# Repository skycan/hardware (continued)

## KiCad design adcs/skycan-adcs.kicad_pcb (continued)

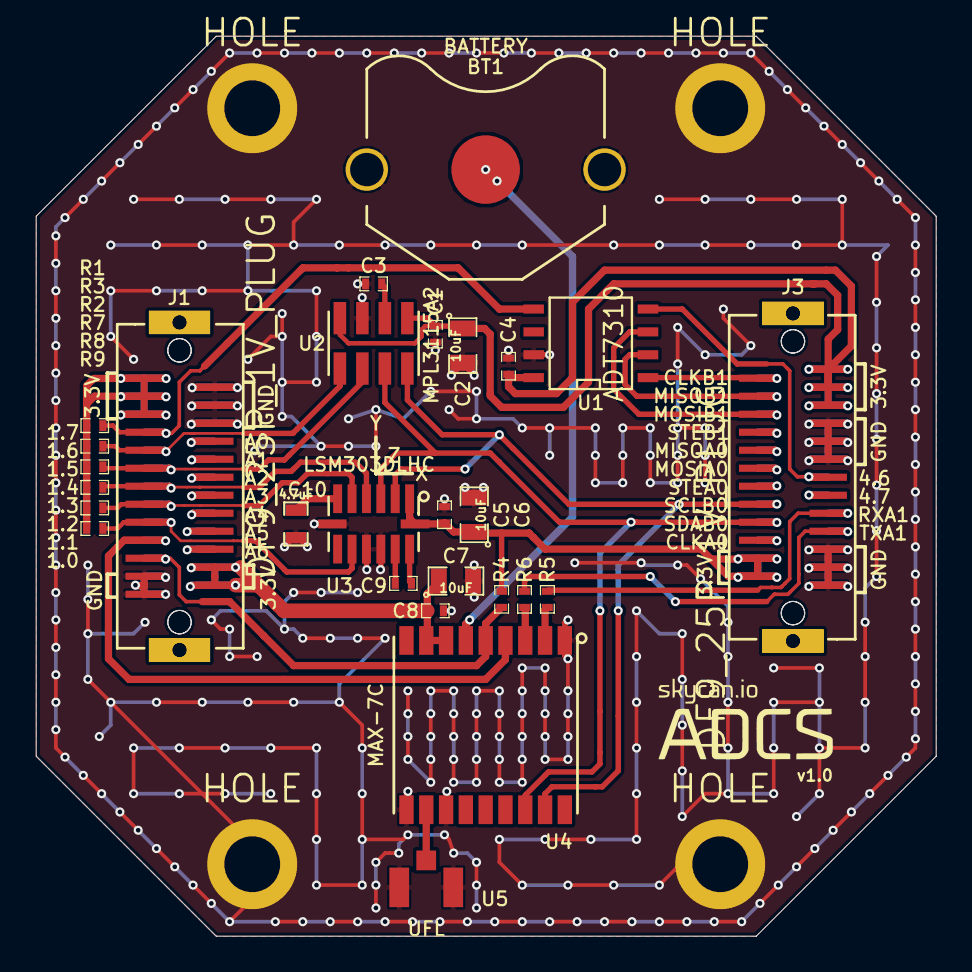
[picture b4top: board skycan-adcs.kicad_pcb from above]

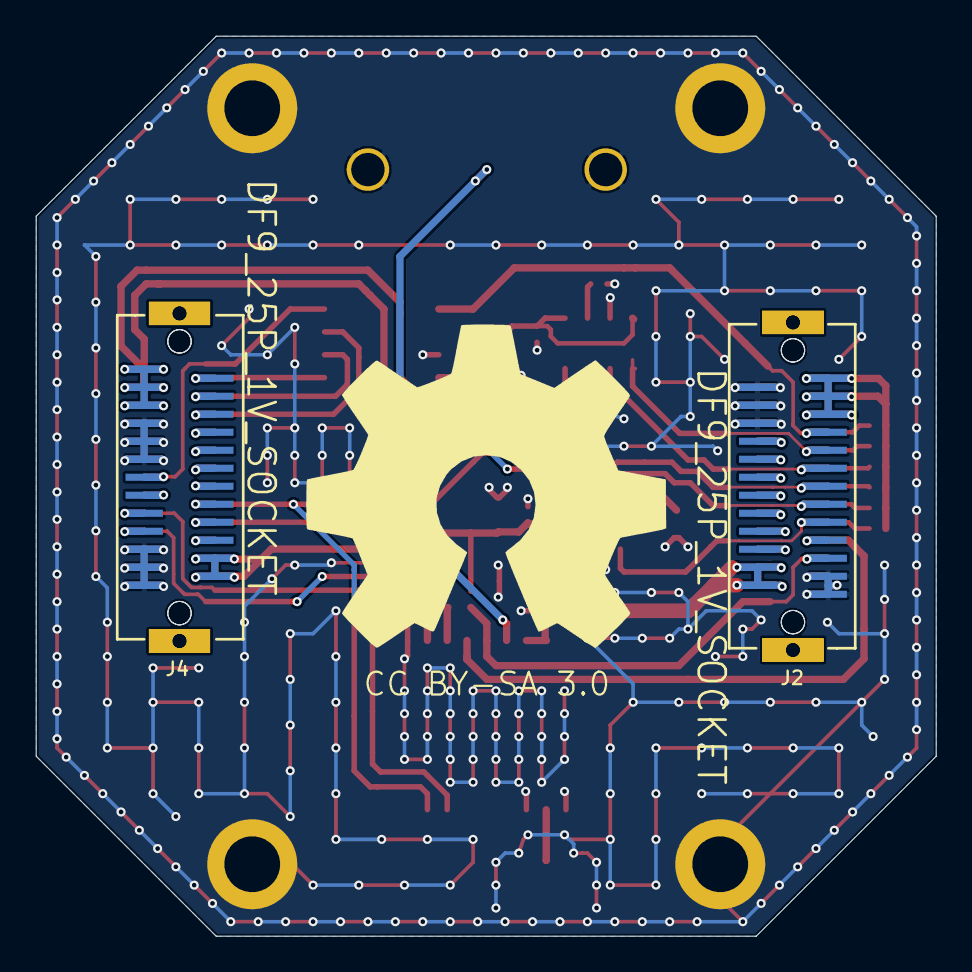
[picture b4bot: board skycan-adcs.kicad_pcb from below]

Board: 2 copper layers, 50.0 x 50.0 mm, 34 parts (2 on the bottom side), 39 nets.

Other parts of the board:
VAL: skycan-adcs-logo

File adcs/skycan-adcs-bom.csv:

Reference,Value,LibPart,Footprint,Qty,Farnell
BT1,BATTERY,device:BATTERY,,1,908642
"C1, C3, C4, C5, C8",100nF,device:C,0402,5,
C10,4.7uF,device:C,0603,1,
"C2, C6, C7",10uF,device:C,0603,3,
C9,220nF,device:C,0402,1,
"J1, J3",DF9_25P_1V_PLUG,skycan:DF9_25P_1V_PLUG,,2,1798379
"J2, J4",DF9_25P_1V_SOCKET,skycan:DF9_25P_1V_SOCKET,,2,1798380
"R1, R2, R3, R4, R7, R8, R9",4.7k,device:R,,7,
"R5, R6",330R,device:R,,2,
U1,ADT7310,skycan:ADT7310,SOIC8,1,2067805
U2,MPL3115A2,skycan:MPL3115A2,LGA8,1,2009084
U3,LSM303DLHC,skycan:LSM303DLHC,LGA-14,1,2068595
U4,MAX-7C,skycan:MAX-7C,,1,
U5,UFL,skycan:UFL,,1,1688077

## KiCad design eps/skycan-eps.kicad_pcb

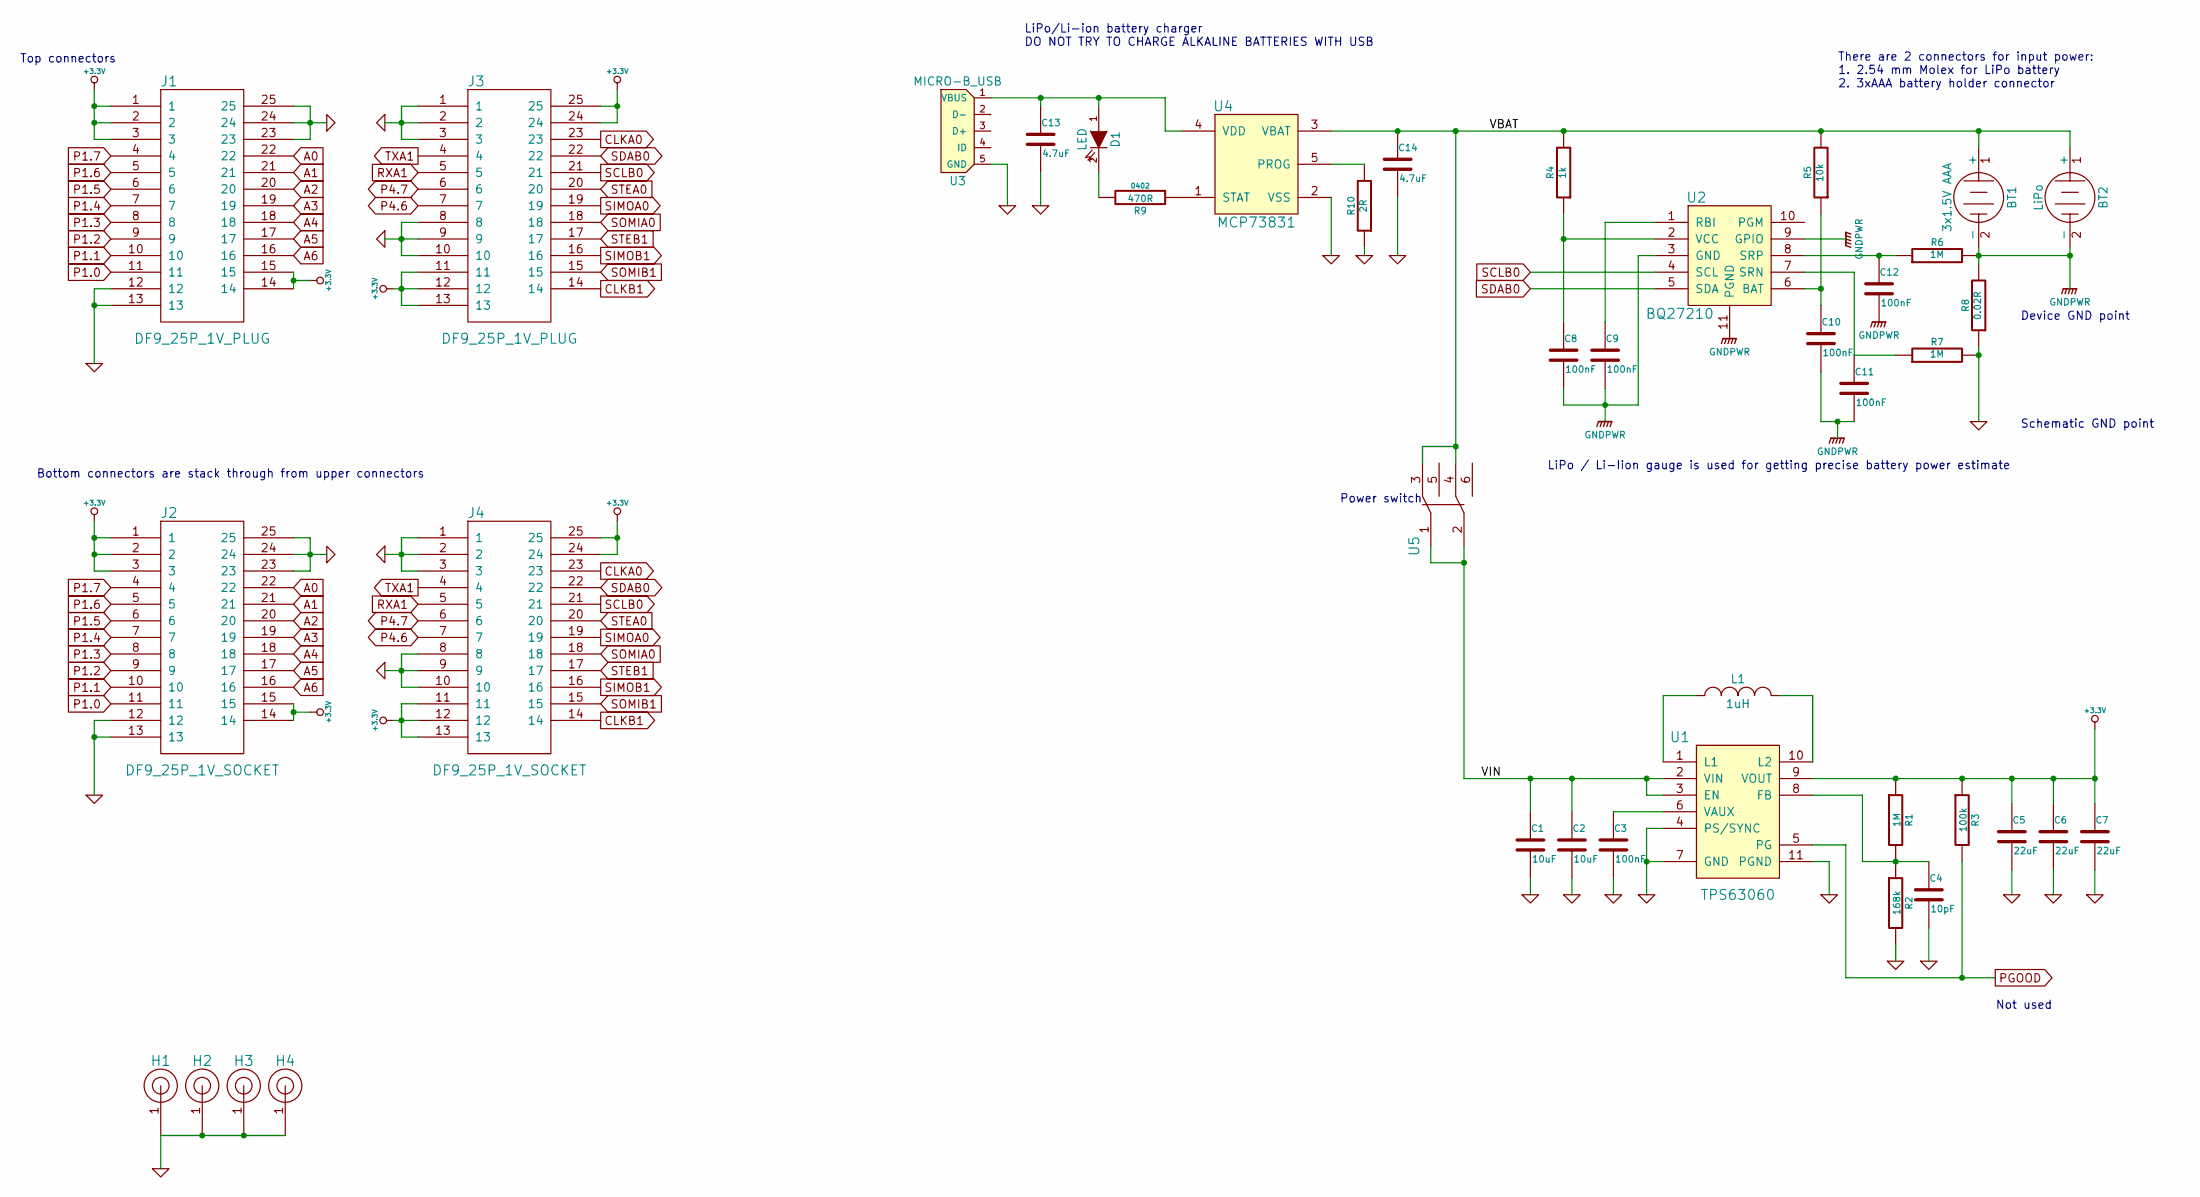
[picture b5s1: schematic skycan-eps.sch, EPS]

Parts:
BT1: 3x1.5V AAA; AA holder; Farnell 1339843
BT2: LiPo
C1, C2: 10uF; 0805
C3, C8, C9, C10, C11, C12: 100nF; 0402
C4: 10pF; 0402
C5, C6, C7: 22uF; 0805
C13, C14: 4.7uF; 0805
D1: LED; 0603
H1, H2, H3, H4: HOLE
J1, J3: DF9_25P_1V_PLUG; Farnell 1798379
J2, J4: DF9_25P_1V_SOCKET; Farnell 1798380
L1: 1uH; 4x4 mm; Farnell 2289214
R1, R6, R7: 1M; 0402
R2: 168k; 0402
R3: 100k; 0402
R4: 1k; 0402
R5: 10k; 0402
R8: 0.02R; 0603
R9: 470R; 0402
R10: 2R; 0402
U1: TPS63060; PWSON-N10; Farnell 2082430
U2: BQ27210; PVSON-N10; Farnell 1754768
U3: MICRO-B_USB; Farnell 2293753
U4: MCP73831; SOT-23-5; Farnell 1332158
U5: SWITCH-DPDT; Farnell 1522047

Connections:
+3.3V: C5.1, C6.1, C7.1, J1.1, J1.2, J1.3, J1.14, J1.15, J2.1, J2.2, J2.3, J2.14, J2.15, J3.11, J3.12, J3.13, J3.24, J3.25, J4.11, J4.12, J4.13, J4.24, J4.25, R1.1, R3.1, U1.9 (VOUT)
/VBAT: BT1.1 (+), BT2.1 (+), C14.1, R4.2, R5.2, U4.3 (VBAT), U5.3, U5.4
/VIN: C1.1, C2.1, U1.2 (VIN), U1.3 (EN), U5.1, U5.2
A0: J1.22, J2.22
A1: J1.21, J2.21
A2: J1.20, J2.20
A3: J1.19, J2.19
A4: J1.18, J2.18
A5: J1.17, J2.17
A6: J1.16, J2.16
CLKA0: J3.23, J4.23
CLKB1: J3.14, J4.14
GND: C1.2, C2.2, C3.2, C4.2, C5.2, C6.2, C7.2, C13.2, C14.2, H1.1, H2.1, H3.1, H4.1, J1.12, J1.13, J1.23, J1.24, J1.25, J2.12, J2.13, J2.23, J2.24, J2.25, J3.1, J3.2, J3.3, J3.8, J3.9, J3.10, J4.1, J4.2, J4.3, J4.8, J4.9, J4.10, R2.2, R7.2, R8.1, R10.1, U1.4 (PS/SYNC), U1.7 (GND), U1.11 (PGND), U3.5 (GND), U4.2 (VSS)
GNDPWR: BT1.2 (-), BT2.2 (-), C8.2, C9.2, C10.2, C11.2, C12.2, R6.2, R8.2, U2.3 (GND), U2.9 (GPIO), U2.11 (PGND)
unnamed: R9.1, U4.1 (STAT)
unnamed: D1.2 (K), R9.2
unnamed: C13.1, D1.1 (A), U3.1 (VBUS), U4.4 (VDD)
unnamed: C3.1, U1.6 (VAUX)
unnamed: C8.1, R4.1, U2.2 (VCC)
unnamed: C10.1, R5.1, U2.6 (BAT)
unnamed: C9.1, U2.1 (RBI)
unnamed: C11.1, R7.1, U2.7 (SRN)
unnamed: R10.2, U4.5 (PROG)
unnamed: L1.1, U1.1 (L1)
unnamed: L1.2, U1.10 (L2)
unnamed: C4.1, R1.2, R2.1, U1.8 (FB)
unnamed: C12.1, R6.1, U2.8 (SRP)
P1.0: J1.11, J2.11
P1.1: J1.10, J2.10
P1.2: J1.9, J2.9
P1.3: J1.8, J2.8
P1.4: J1.7, J2.7
P1.5: J1.6, J2.6
P1.6: J1.5, J2.5
P1.7: J1.4, J2.4
P4.6: J3.7, J4.7
P4.7: J3.6, J4.6
PGOOD: R3.2, U1.5 (PG)
RXA1: J3.5, J4.5
SCLB0: J3.21, J4.21, U2.4 (SCL)
SDAB0: J3.22, J4.22, U2.5 (SDA)
SIMOA0: J3.19, J4.19
SIMOB1: J3.16, J4.16
SOMIA0: J3.18, J4.18
SOMIB1: J3.15, J4.15
STEA0: J3.20, J4.20
STEB1: J3.17, J4.17
TXA1: J3.4, J4.4

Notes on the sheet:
Top connectors
Bottom connectors are stack through from upper connectors
There are 2 connectors for input power: 1. 2.54 mm Molex for LiPo battery 2. 3xAAA battery holder connector
LiPo / Li-Iion gauge is used for getting precise battery power estimate
Not used
Device GND point
Schematic GND point
LiPo/Li-ion battery charger DO NOT TRY TO CHARGE ALKALINE BATTERIES WITH USB
Power switch

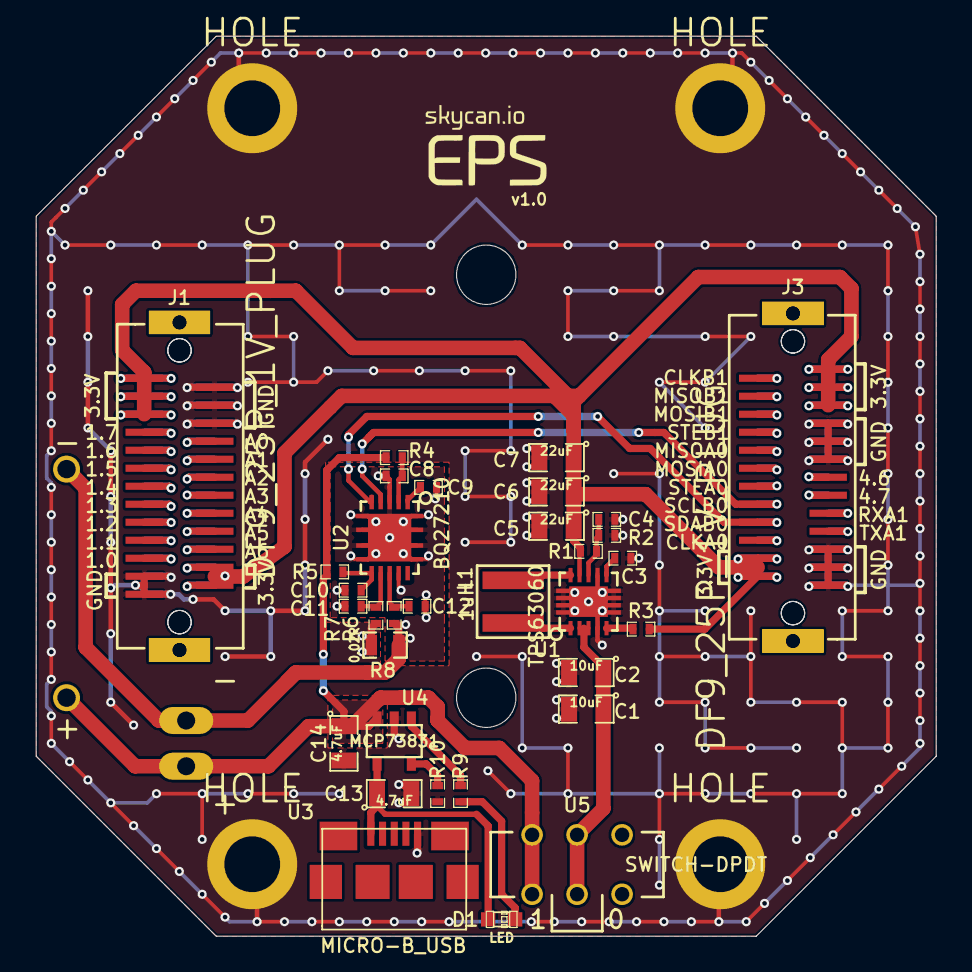
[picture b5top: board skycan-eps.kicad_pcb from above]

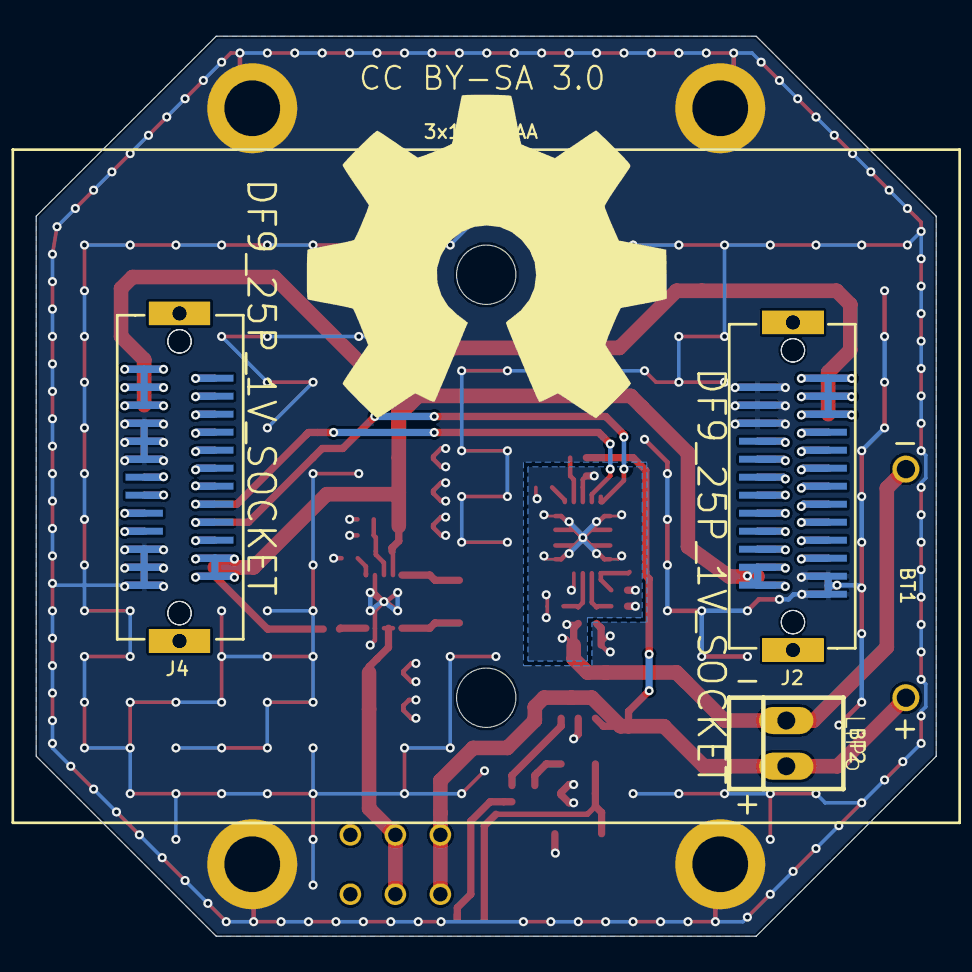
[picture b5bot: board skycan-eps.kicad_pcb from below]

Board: 2 copper layers, 50.0 x 50.0 mm, 42 parts (4 on the bottom side), 48 nets.

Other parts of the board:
VAL: skycan-eps-logo

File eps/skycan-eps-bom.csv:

Reference,Value,LibPart,Footprint,Qty,Farnell
BT1,3x1.5V AAA,device:BATTERY,AA holder,1,1339843
BT2,LiPo,device:BATTERY,LiPo,1,
"C1, C2",10uF,device:C,0805,2,
"C10, C11, C12, C3, C8, C9",100nF,device:C,0402,6,
"C13, C14",4.7uF,device:C,0805,2,
C4,10pF,device:C,0402,1,
"C5, C6, C7",22uF,device:C,0805,3,
D1,LED,device:LED,0603,1,
"J1, J3",DF9_25P_1V_PLUG,skycan:DF9_25P_1V_PLUG,,2,1798379
"J2, J4",DF9_25P_1V_SOCKET,skycan:DF9_25P_1V_SOCKET,,2,1798380
L1,1uH,device:INDUCTOR_SMALL,4x4 mm,1,2289214
"R1, R6, R7",1M,device:R,0402,3,
R10,2R,device:R,0402,1,
R2,168k,device:R,0402,1,
R3,100k,device:R,0402,1,
R4,1k,device:R,0402,1,
R5,10k,device:R,0402,1,
R8,0.02R,device:R,0603,1,
R9,470R,device:R,0402,1,
U1,TPS63060,skycan:TPS63060,PWSON-N10,1,2082430
U2,BQ27210,skycan:BQ27210,PVSON-N10,1,1754768
U3,MICRO-B_USB,skycan:MICRO-B_USB,,1,2293753
U4,MCP73831,skycan:MCP73831,SOT-23-5,1,1332158
U5,SWITCH-DPDT,skycan:SWITCH-DPDT,,1,1522047

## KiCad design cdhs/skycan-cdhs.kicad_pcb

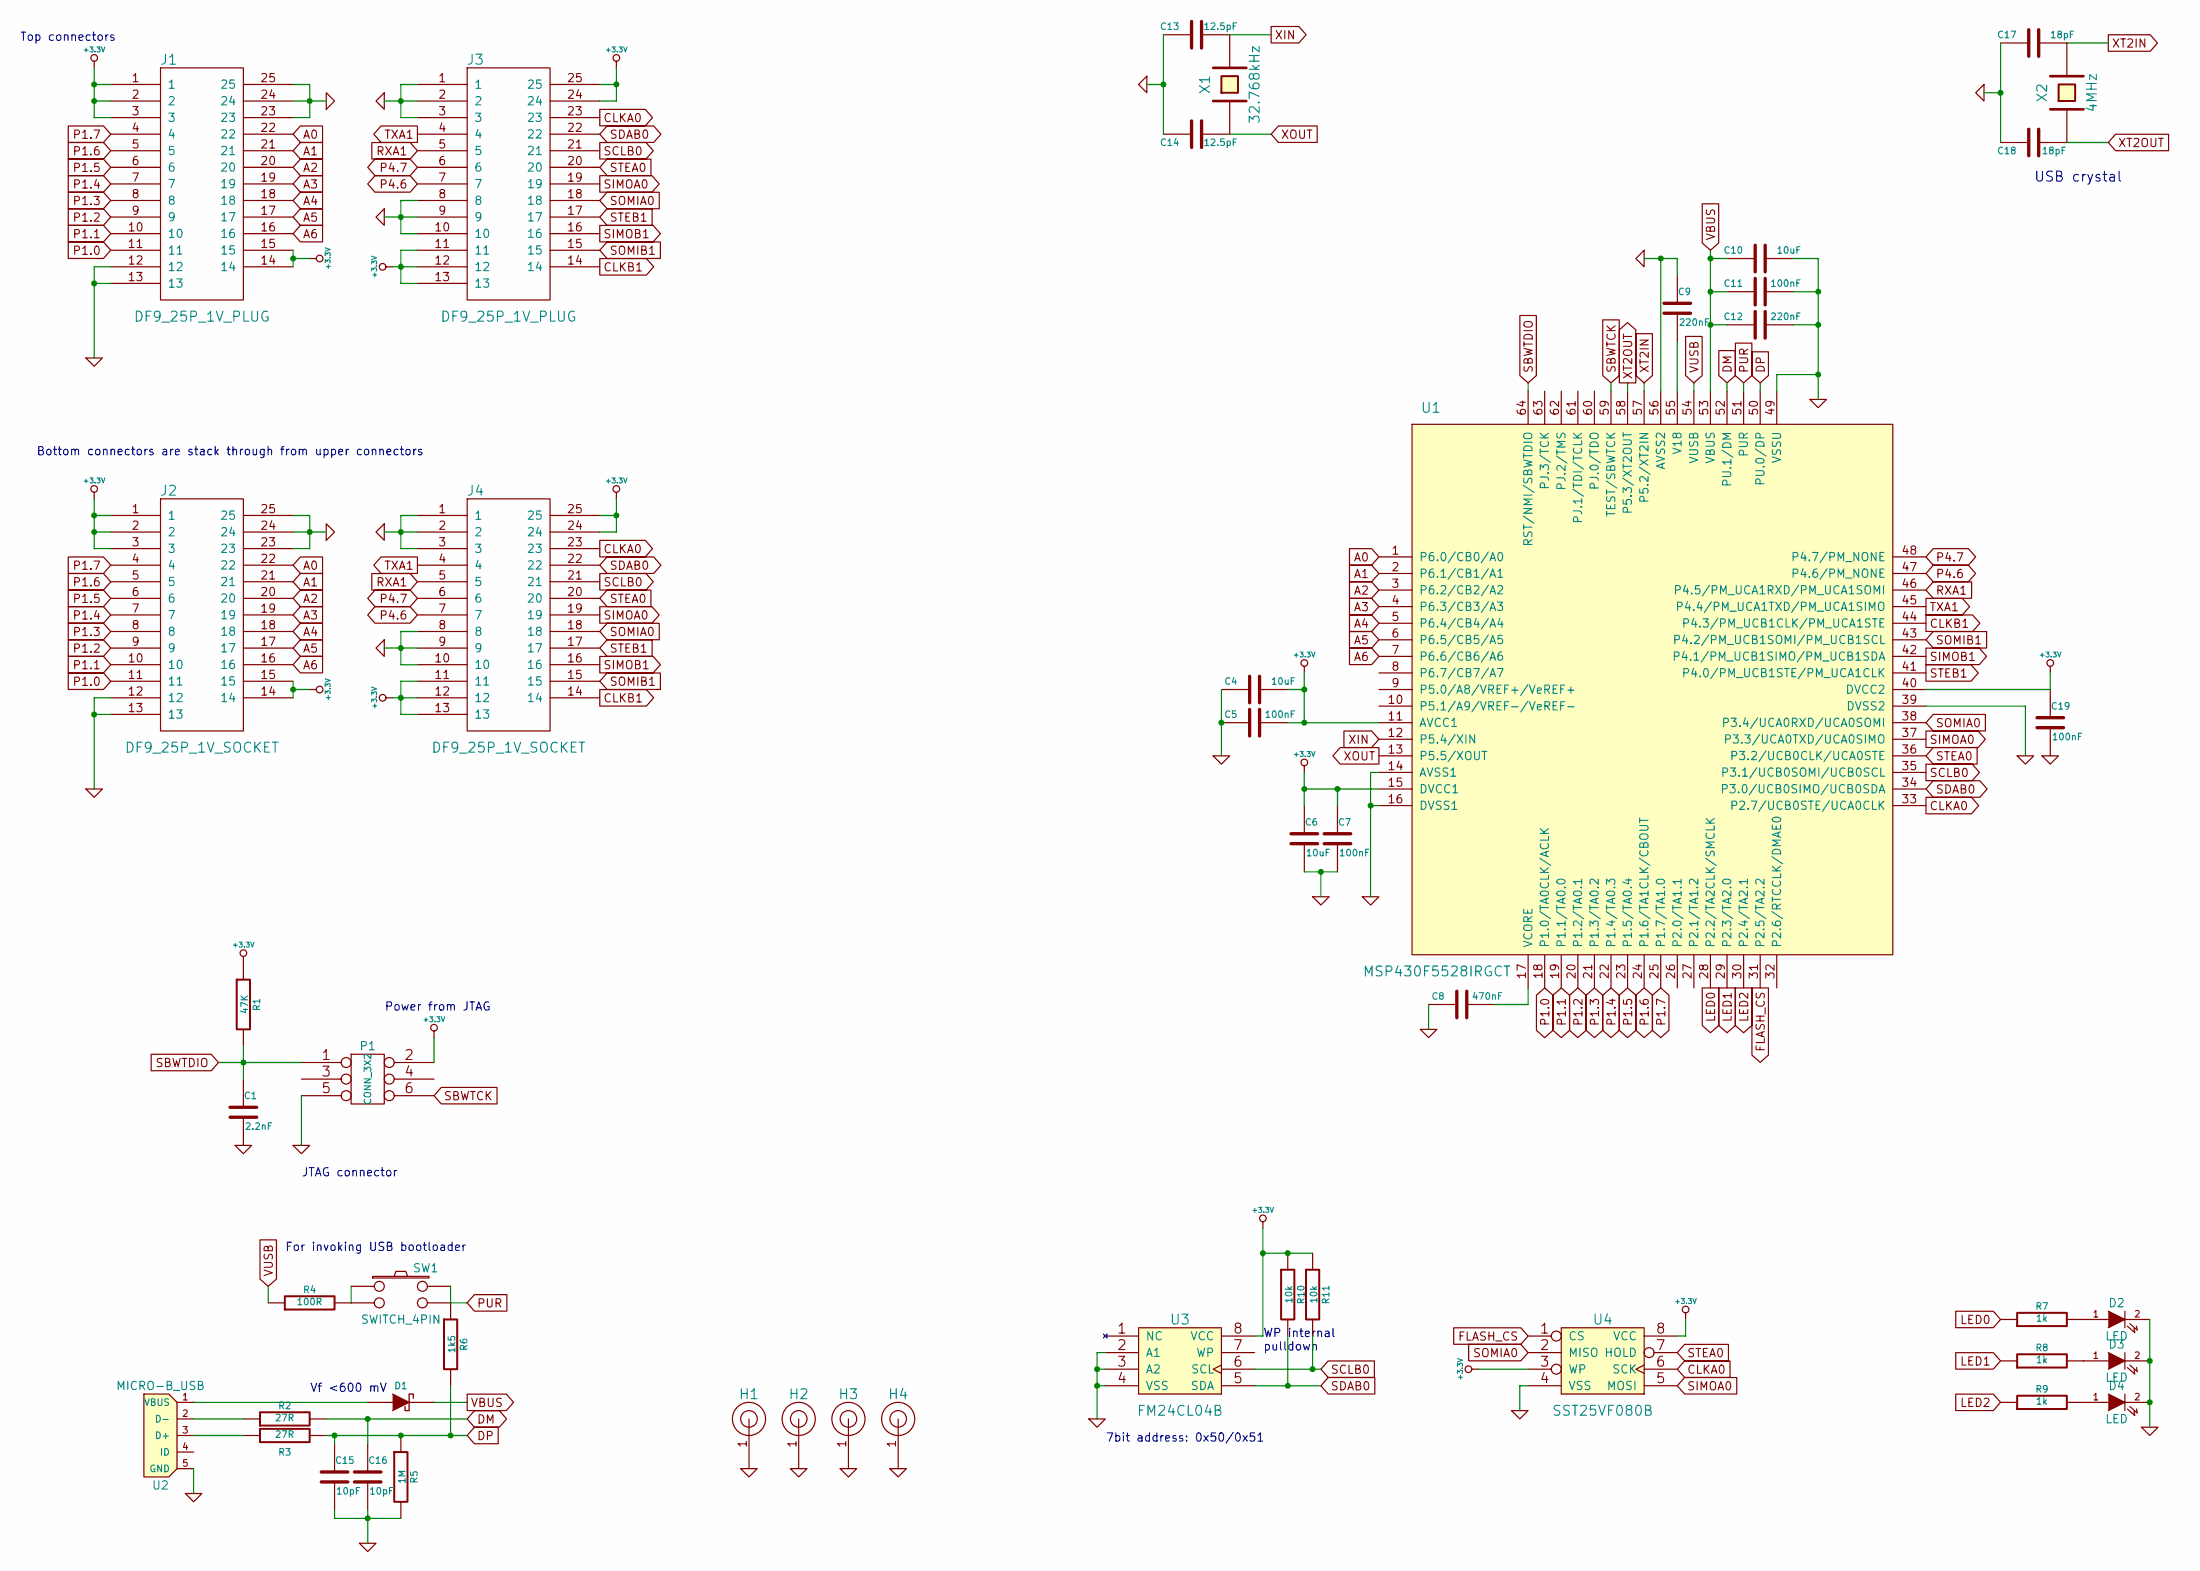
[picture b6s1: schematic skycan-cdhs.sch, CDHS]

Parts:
C1: 2.2nF; 0402
C4, C6, C10: 10uF; 0603
C5, C7, C11, C19: 100nF; 0402
C8: 470nF; 0402
C9, C12: 220nF; 0402
C13, C14: 12.5pF; 0402
C15, C16: 10pF; 0402
C17, C18: 18pF; 0402
D1: DIODESCH3PIN; Farnell 1056832
D2, D3, D4: LED; 0603
H1, H2, H3, H4: HOLE
J1, J3: DF9_25P_1V_PLUG; 1 mm 2 rows 25 pins; Farnell 1798379
J2, J4: DF9_25P_1V_SOCKET; 1 mm 2 rows 25 pins; Farnell 1798380
P1: CONN_3X2; smd 2x3 1.27 mm
R1: 47K; 0402
R2, R3: 27R; 0402
R4: 100R; 0402
R5: 1M; 0402
R6: 1k5; 0402
R7, R8, R9: 1k; 0402
R10, R11: 10k; 0402
SW1: SWITCH_4PIN; Farnell 2056841
U1: MSP430F5528IRGCT; VQFN64; Farnell 1866820
U2: MICRO-B_USB; 5 pads; Farnell 2293753
U3: FM24CL04B; SOIC8; Farnell 2077746
U4: SST25VF080B; SOIC8; Farnell 1871942
X1: 32.768kHz; 4.9 x 1.8 mm; Farnell 2101352
X2: 4MHz; HC49; Farnell 1652553

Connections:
+3.3V: C4.2, C5.2, C6.1, C7.1, C19.1, J1.1, J1.2, J1.3, J1.14, J1.15, J2.1, J2.2, J2.3, J2.14, J2.15, J3.11, J3.12, J3.13, J3.24, J3.25, J4.11, J4.12, J4.13, J4.24, J4.25, P1.2, R1.1, R10.1, R11.1, U1.11 (AVCC1), U1.15 (DVCC1), U1.40 (DVCC2), U3.8 (VCC), U4.3 (WP), U4.8 (VCC)
A0: J1.22, J2.22, U1.1 (P6.0/CB0/A0)
A1: J1.21, J2.21, U1.2 (P6.1/CB1/A1)
A2: J1.20, J2.20, U1.3 (P6.2/CB2/A2)
A3: J1.19, J2.19, U1.4 (P6.3/CB3/A3)
A4: J1.18, J2.18, U1.5 (P6.4/CB4/A4)
A5: J1.17, J2.17, U1.6 (P6.5/CB5/A5)
A6: J1.16, J2.16, U1.7 (P6.6/CB6/A6)
CLKA0: J3.23, J4.23, U1.33 (P2.7/UCB0STE/UCA0CLK), U4.6 (SCK)
CLKB1: J3.14, J4.14, U1.44 (P4.3/PM_UCB1CLK/PM_UCA1STE)
DM: C16.1, R2.2, U1.52 (PU.1/DM)
DP: C15.1, R3.2, R5.1, R6.2, U1.50 (PU.0/DP)
FLASH_CS: U1.31 (P2.5/TA2.2), U4.1 (CS)
GND: C1.2, C4.1, C5.1, C6.2, C7.2, C8.1, C9.1, C10.2, C11.2, C12.2, C13.1, C14.1, C15.2, C16.2, C17.1, C18.1, C19.2, D2.2 (K), D3.2 (K), D4.2 (K), H1.1, H2.1, H3.1, H4.1, J1.12, J1.13, J1.23, J1.24, J1.25, J2.12, J2.13, J2.23, J2.24, J2.25, J3.1, J3.2, J3.3, J3.8, J3.9, J3.10, J4.1, J4.2, J4.3, J4.8, J4.9, J4.10, P1.5, R5.2, U1.14 (AVSS1), U1.16 (DVSS1), U1.39 (DVSS2), U1.49 (VSSU), U1.56 (AVSS2), U2.5 (GND), U3.2 (A1), U3.3 (A2), U3.4 (VSS), U4.4 (VSS)
LED0: R7.1, U1.28 (P2.2/TA2CLK/SMCLK)
LED1: R8.1, U1.29 (P2.3/TA2.0)
LED2: R9.1, U1.30 (P2.4/TA2.1)
unnamed: R4.2, SW1.1, SW1.2
unnamed: D1.1 (A), U2.1 (VBUS)
unnamed: D2.1 (A), R7.2
unnamed: D3.1 (A), R8.2
unnamed: D4.1 (A), R9.2
unnamed: R3.1, U2.3 (D+)
unnamed: C9.2, U1.55 (V18)
unnamed: C8.2, U1.17 (VCORE)
unnamed: R2.1, U2.2 (D-)
P1.0: J1.11, J2.11, U1.18 (P1.0/TA0CLK/ACLK)
P1.1: J1.10, J2.10, U1.19 (P1.1/TA0.0)
P1.2: J1.9, J2.9, U1.20 (P1.2/TA0.1)
P1.3: J1.8, J2.8, U1.21 (P1.3/TA0.2)
P1.4: J1.7, J2.7, U1.22 (P1.4/TA0.3)
P1.5: J1.6, J2.6, U1.23 (P1.5/TA0.4)
P1.6: J1.5, J2.5, U1.24 (P1.6/TA1CLK/CBOUT)
P1.7: J1.4, J2.4, U1.25 (P1.7/TA1.0)
P4.6: J3.7, J4.7, U1.47 (P4.6/PM_NONE)
P4.7: J3.6, J4.6, U1.48 (P4.7/PM_NONE)
PUR: R6.1, SW1.3, SW1.4, U1.51 (PUR)
RXA1: J3.5, J4.5, U1.46 (P4.5/PM_UCA1RXD/PM_UCA1SOMI)
SBWTCK: P1.6, U1.59 (TEST/SBWTCK)
SBWTDIO: C1.1, P1.1, R1.2, U1.64 (RST/NMI/SBWTDIO)
SCLB0: J3.21, J4.21, R11.2, U1.35 (P3.1/UCB0SOMI/UCB0SCL), U3.6 (SCL)
SDAB0: J3.22, J4.22, R10.2, U1.34 (P3.0/UCB0SIMO/UCB0SDA), U3.5 (SDA)
SIMOA0: J3.19, J4.19, U1.37 (P3.3/UCA0TXD/UCA0SIMO), U4.5 (MOSI)
SIMOB1: J3.16, J4.16, U1.42 (P4.1/PM_UCB1SIMO/PM_UCB1SDA)
SOMIA0: J3.18, J4.18, U1.38 (P3.4/UCA0RXD/UCA0SOMI), U4.2 (MISO)
SOMIB1: J3.15, J4.15, U1.43 (P4.2/PM_UCB1SOMI/PM_UCB1SCL)
STEA0: J3.20, J4.20, U1.36 (P3.2/UCB0CLK/UCA0STE), U4.7 (HOLD)
STEB1: J3.17, J4.17, U1.41 (P4.0/PM_UCB1STE/PM_UCA1CLK)
TXA1: J3.4, J4.4, U1.45 (P4.4/PM_UCA1TXD/PM_UCA1SIMO)
VBUS: C10.1, C11.1, C12.1, D1.3 (K), U1.53 (VBUS)
VUSB: R4.1, U1.54 (VUSB)
XIN: C13.2, U1.12 (P5.4/XIN), X1.2
XOUT: C14.2, U1.13 (P5.5/XOUT), X1.1
XT2IN: C17.2, U1.57 (P5.2/XT2IN), X2.2
XT2OUT: C18.2, U1.58 (P5.3/XT2OUT), X2.1

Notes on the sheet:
Power from JTAG
JTAG connector
USB crystal
For invoking USB bootloader
Vf <600 mV
Top connectors
Bottom connectors are stack through from upper connectors
WP internal pulldown
7bit address: 0x50/0x51

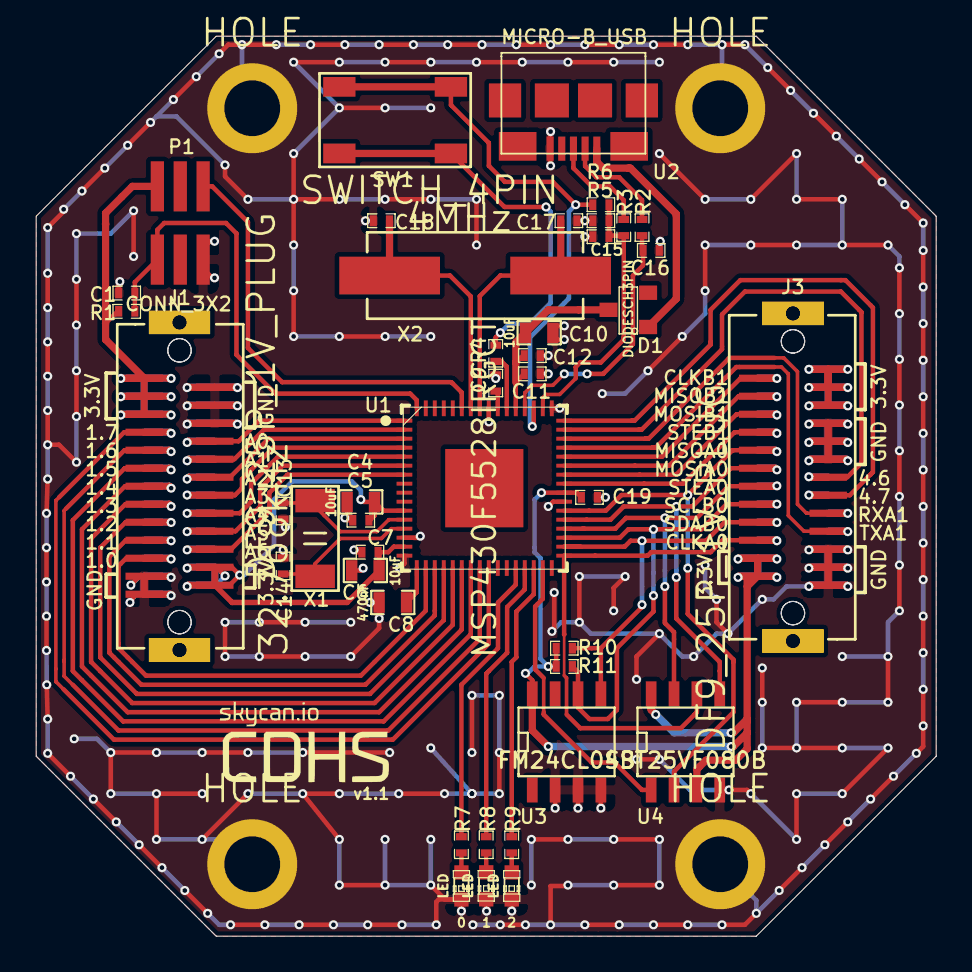
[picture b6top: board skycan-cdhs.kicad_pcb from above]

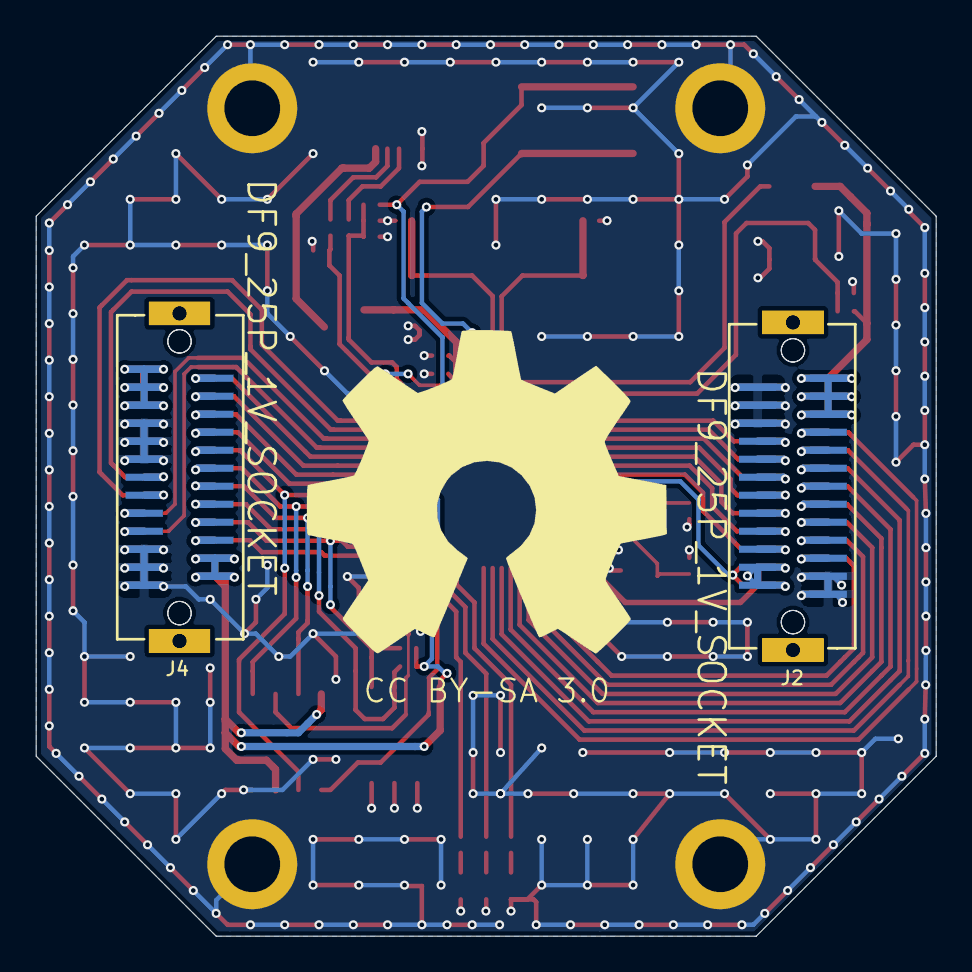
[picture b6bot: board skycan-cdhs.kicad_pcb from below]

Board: 2 copper layers, 50.0 x 50.0 mm, 49 parts (2 on the bottom side), 55 nets.

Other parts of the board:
VAL: skycan-cdhs-logo

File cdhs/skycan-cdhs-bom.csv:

Source:,/media/sf_Development/github/skycan-hardware/cdhs/skycan-cdhs.sch
Date:,P 15 sept  2013 12:53:36 EEST
Tool:,eeschema (2013-09-06 BZR 4312)-stable
Component Count:,44

Components:

Reference,Value,LibPart,Footprint,Qty,Farnell
C1,2.2nF,device:C,0402,1,
"C10, C4, C6",10uF,device:C,0603,3,
"C11, C19, C5, C7",100nF,device:C,0402,4,
"C12, C9",220nF,device:C,0402,2,
"C13, C14",12.5pF,device:C,0402,2,
"C15, C16",10pF,device:C,0402,2,
"C17, C18",18pF,device:C,0402,2,
C8,470nF,device:C,0402,1,
D1,DIODESCH3PIN,skycan:DIODESCH3PIN,SOT-23,1,1056832
"D2, D3, D4",LED,device:LED,0603,3,
"J1, J3",DF9_25P_1V_PLUG,skycan:DF9_25P_1V_PLUG,1 mm 2 rows 25 pins,2,1798379
"J2, J4",DF9_25P_1V_SOCKET,skycan:DF9_25P_1V_SOCKET,1 mm 2 rows 25 pins,2,1798380
P1,CONN_3X2,conn:CONN_3X2,smd 2x3 1.27 mm,1,
R1,47K,device:R,0402,1,
"R10, R11",10k,device:R,0402,2,
"R2, R3",27R,device:R,0402,2,
R4,100R,device:R,0402,1,
R5,1M,device:R,0402,1,
R6,1k5,device:R,0402,1,
"R7, R8, R9",1k,device:R,0402,3,
SW1,SWITCH_4PIN,skycan:SWITCH_4PIN,,1,2056841
U1,MSP430F5528IRGCT,skycan:MSP430F5528IRGCT,VQFN64,1,1866820
U2,MICRO-B_USB,skycan:MICRO-B_USB,5 pads,1,2293753
U3,FM24CL04B,skycan:FRAM-I2C,SOIC8,1,2077746
U4,SST25VF080B,skycan:FRAM,SOIC8,1,1871942
X1,32.768kHz,device:CRYSTAL,4.9 x 1.8 mm,1,2101352
X2,4MHz,device:CRYSTAL,HC49,1,1652553

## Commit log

2013-08-20 Update LICENSE
2013-08-20 Added CDHS board
2013-08-20 Tweaked cdhs board silkscreen
2013-08-20 Added CDHS v1.0 gerberfiles
2013-09-07 Added EPS board design files.
2013-09-07 Added EPS logo module
2013-09-07 Added EPS logo svg file
2013-09-07 CDHS edge is generated for all layers
2013-09-07 Added more modules to kicadlib
2013-09-11 Added skycan lib.
    It replaces all the other libs in the future, EPS board already uses it. CDHS must be migrated.
2013-09-11 Update lib files.
2013-09-11 EPS board now uses only skycan lib.
2013-09-14 Updated skycan lib
2013-09-14 Now CDHS uses only skycan lib Mounting holes connected to gnd
2013-09-14 Removed old libs
2013-09-14 Added tool for merging drill files
2013-09-14 Added tool for preparring gerber files for manufacturing
2013-09-14 Updated cdhs silkscreen to v1.1
2013-09-14 Updated cdhs gerber files
    Consider it as v1.1
2013-09-15 Updated pushbutton name and some Farnell codes to lib
2013-09-15 Added Farnell codes and footprints to CDHS schematic
2013-09-15 Added simple BOM generation script
2013-09-15 Added diode footprint info to CDHS
2013-09-15 Update kicadlib
2013-09-15 Now BOM generator groups values
2013-09-15 Added CDHS BOM file
2013-09-15 Added Farnell codes to EPS schematic
2013-09-15 Added EPS BOM file
2013-09-15 Updated bom generator to support github csv rendering
2013-09-15 Updated BOM files to support github rendering
2013-09-15 Added more vias to EPS pwrgnd plane
2013-09-15 Added EPS gerber files
2013-09-18 Updated CDHS BOM
2013-09-18 Fixed EPS charger prog resistor value
2013-09-18 Improved EPS main Vreg divider value
2013-09-18 Added EPS power measurement resistor Farnell code
2013-09-19 Changed CDHS reset switch Farnell code
2013-09-19 Added I2C address info to EPS schem
2013-10-08 Added ADCS components to lib
2013-10-08 Added initial ADCS schematic
2013-10-19 Adde GPS logo
2013-10-19 Added GPS board components to library
2013-10-19 Added work in progress GPS antenna board.
2013-10-23 GPS layout finished.
2013-10-23 Added GPS gerbers.
2013-10-23 Changed SMA lib.
2013-10-23 Added SMA Farnell code sch.
2013-10-23 Reworked GPS pcb.
2013-10-23 Regenerated GPS gerbers.
2013-10-23 Added GPS BOM file.
2013-10-25 Added ADCS board modules to lib.
2013-10-25 Added footprints to ADCS cmp. Save all.
2013-10-31 adcs routing inprogress
2013-11-02 punch of stuff routed in adcs
2013-11-04 signals routed
2013-11-05 add two more inner layers to gps
2013-11-05 generate 4 layer gps gerbers
2013-11-06 add outline as separate layer to gps gerbers
2013-11-09 finish adcs routing
2013-11-09 save skycan.mod
2013-11-10 add adcs logo to skycap lib
2013-11-10 add adcs svg logo
2013-11-10 finish adcs layout
2013-11-13 make adcs layout a little nicer
2013-11-13 add adcs gerbers
2013-11-13 add adcs bom
2013-11-14 gerber-cleaner now generates outline as .GKO file
2013-11-14 regenerate adcs berbers, add outline as .GKO file
2013-11-14 save adcs layout settings
2013-11-20 add skycan-dbg-logo.svg
2013-11-20 add dbg logo to lib
2013-11-20 add dbg schematic and layout
2013-11-20 add dbg bom
2013-11-20 add dbg 2 layer gerbers
2013-11-21 add inner gnd layers for 4 layer dbg board
2013-11-21 generate 4 layer dbg gerbers
2013-11-21 add 4 layer support to gerber-cleaner.py
2013-11-21 save dog layerselection
2014-01-20 add blank com schematic and pcb
2014-01-22 add CC1120, LDO and TCXO to skycap.lib
2014-01-22 CC1120 with TCXO placed, matching is WIP
2014-01-24 finish cc1120 schematic
2014-01-30 add NRFf8001, Johanson balun and chip antenna to lib
2014-01-30 add NRF8001, Johanson balun and chip antenna to COM schematic
    schematic is now ready
2014-02-01 add EP pin to NRF8001 symbol
2014-02-01 add footprints to balun, antenna, oscillators
2014-02-01 generate nets and assigne footprins
2014-02-01 components placed to pcb
    routing not yet started
2014-02-02 swapped some nrf8001 and cc1120 pins
2014-02-02 cc1120, nrf8001 digital stuff routed RF still to do
2014-02-02 update cache-lib
2014-02-17 add note about BAL1 BAL2 trace lengths
2014-02-17 com pcb routed and ground planes ready
2014-03-03 add com logo
2014-03-03 add com logo to pcb
    only via stitching to do
2014-03-04 com board via stitching ready
2014-03-04 add part numbers, generate bom
2014-03-04 sync com schematic and pcb
2014-03-04 update com pcb
2014-03-04 add com gerbers
